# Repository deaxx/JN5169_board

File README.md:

# JN5169_board
mini-dev board on E75-2G4M10S

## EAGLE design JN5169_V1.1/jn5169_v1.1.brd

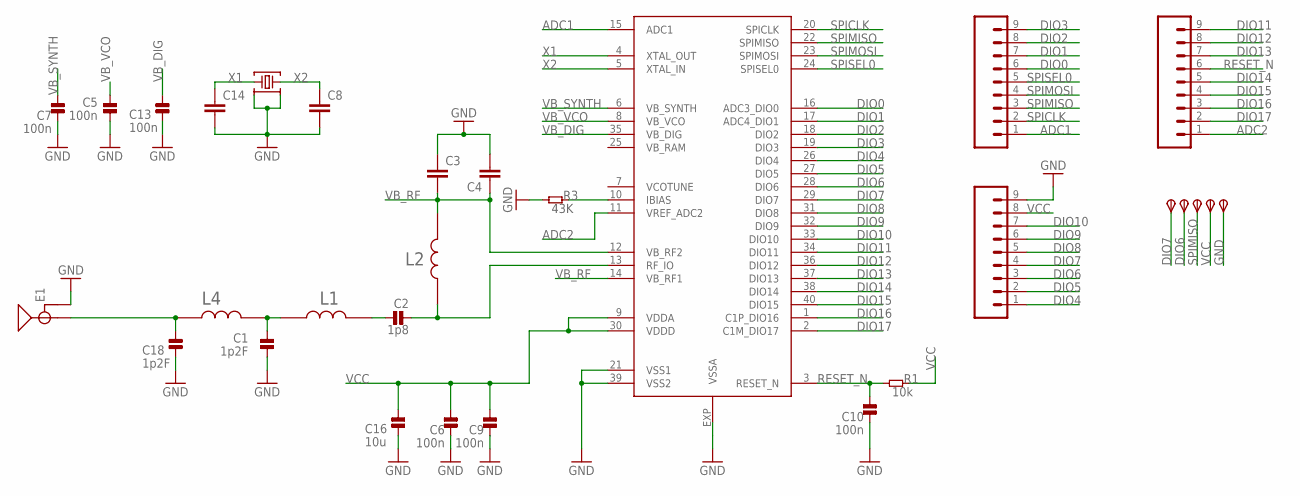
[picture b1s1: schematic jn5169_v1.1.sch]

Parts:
C1, C18: 1p2F; _PKG_C_0402
C2: 1p8; _PKG_C_0402
C3: 100n; CAPC1005X40N
C4: 47pf; CAPC1005X40N
C5, C6, C7, C9, C10, C13: 100n; _PKG_C_0402
C8, C14: 12p; CAPC1005X40N
C16: 10u; _PKG_C_0805
E1: ANTENNA-GROUNDEDTRACE-15.2MM; TRACE_ANTENNA_2.4GHZ_15.2MM
GND: TPSTP11R; TP11R
J1, J2, J3: CONN_051.27MM; 1X05_1.27MM
L1: 3n3H; INDC1005X40N
L2: 1n5H; INDC1005X40N
L4: 2n7H; INDC1005X40N
R1: 10k; _PKG_C_0402
R3: 43K; _PKG_C_0402
RX: TPSTP11R; TP11R
TDO: TPSTP11R; TP11R
TX: TPSTP11R; TP11R
U$1: JN5168/A02Z; QFN50P600X600X100-41N
VCC: TPSTP11R; TP11R
Y1: 32MHZ; XTAL-4P-2016

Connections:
ADC1: J1.1, U$1.15 (ADC1)
ADC2: J3.1, U$1.11 (VREF_ADC2)
DIO0: J1.6, U$1.16 (ADC3_DIO0)
DIO1: J1.7, U$1.17 (ADC4_DIO1)
DIO2: J1.8, U$1.18 (DIO2)
DIO3: J1.9, U$1.19 (DIO3)
DIO4: J2.1, U$1.26 (DIO4)
DIO5: J2.2, U$1.27 (DIO5)
DIO6: J2.3, TX.TP, U$1.28 (DIO6)
DIO7: J2.4, RX.TP, U$1.29 (DIO7)
DIO8: J2.5, U$1.31 (DIO8)
DIO9: J2.6, U$1.32 (DIO9)
DIO10: J2.7, U$1.33 (DIO10)
DIO11: J3.9, U$1.34 (DIO11)
DIO12: J3.8, U$1.36 (DIO12)
DIO13: J3.7, U$1.37 (DIO13)
DIO14: J3.5, U$1.38 (DIO14)
DIO15: J3.4, U$1.40 (DIO15)
DIO16: J3.3, U$1.1 (C1P_DIO16)
DIO17: J3.2, U$1.2 (C1M_DIO17)
GND: C1.1, C3.1, C4.2, C5.1, C6.1, C7.1, C8.2, C9.1, C10.1, C13.2, C14.2, C16.2, C18.2, E1.GND, GND.TP, J2.9, R3.2, U$1.21 (VSS1), U$1.39 (VSS2), U$1.EXP (VSSA), Y1.2, Y1.4
unnamed: C2.2, L1.2
unnamed: C2.1, L2.1, U$1.13 (RF_IO)
unnamed: C1.2, L1.1, L4.2
unnamed: C18.1, E1.ANT (SIGNAL), L4.1
unnamed: R3.1, U$1.10 (IBIAS)
RESET_N: C10.2, J3.6, R1.2, U$1.3 (RESET_N)
SPICLK: J1.2, U$1.20 (SPICLK)
SPIMISO: J1.3, TDO.TP, U$1.22 (SPIMISO)
SPIMOSI: J1.4, U$1.23 (SPIMOSI)
SPISEL0: J1.5, U$1.24 (SPISEL0)
VB_DIG: C13.1, U$1.35 (VB_DIG)
VB_RAM: U$1.25 (VB_RAM)
VB_RF: C3.2, C4.1, L2.2, U$1.12 (VB_RF2), U$1.14 (VB_RF1)
VB_SYNTH: C7.2, U$1.6 (VB_SYNTH)
VB_VCO: C5.2, U$1.8 (VB_VCO)
VCC: C6.2, C9.2, C16.1, J2.8, R1.1, U$1.9 (VDDA), U$1.30 (VDDD), VCC.TP
VCOTUNE: U$1.7 (VCOTUNE)
X1: C14.1, U$1.4 (XTAL_OUT), Y1.1
X2: C8.1, U$1.5 (XTAL_IN), Y1.3

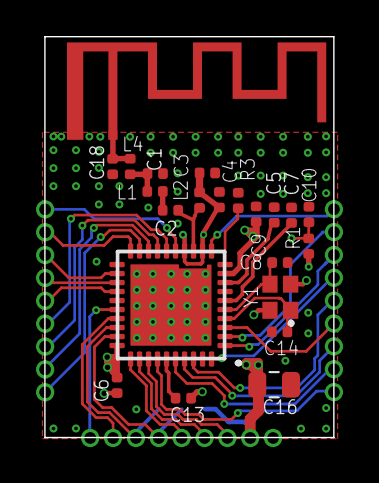
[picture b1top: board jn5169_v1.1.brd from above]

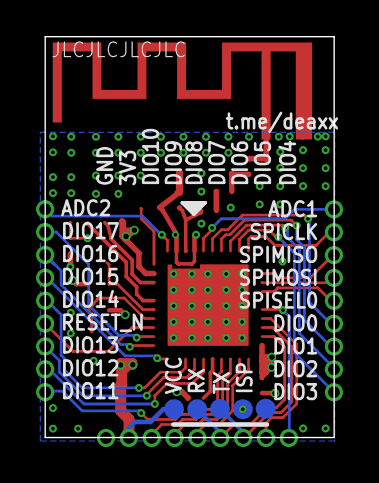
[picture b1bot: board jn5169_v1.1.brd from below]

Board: 4 copper layers, 16.1 x 22.3 mm, 30 parts (5 on the bottom side), 38 nets.

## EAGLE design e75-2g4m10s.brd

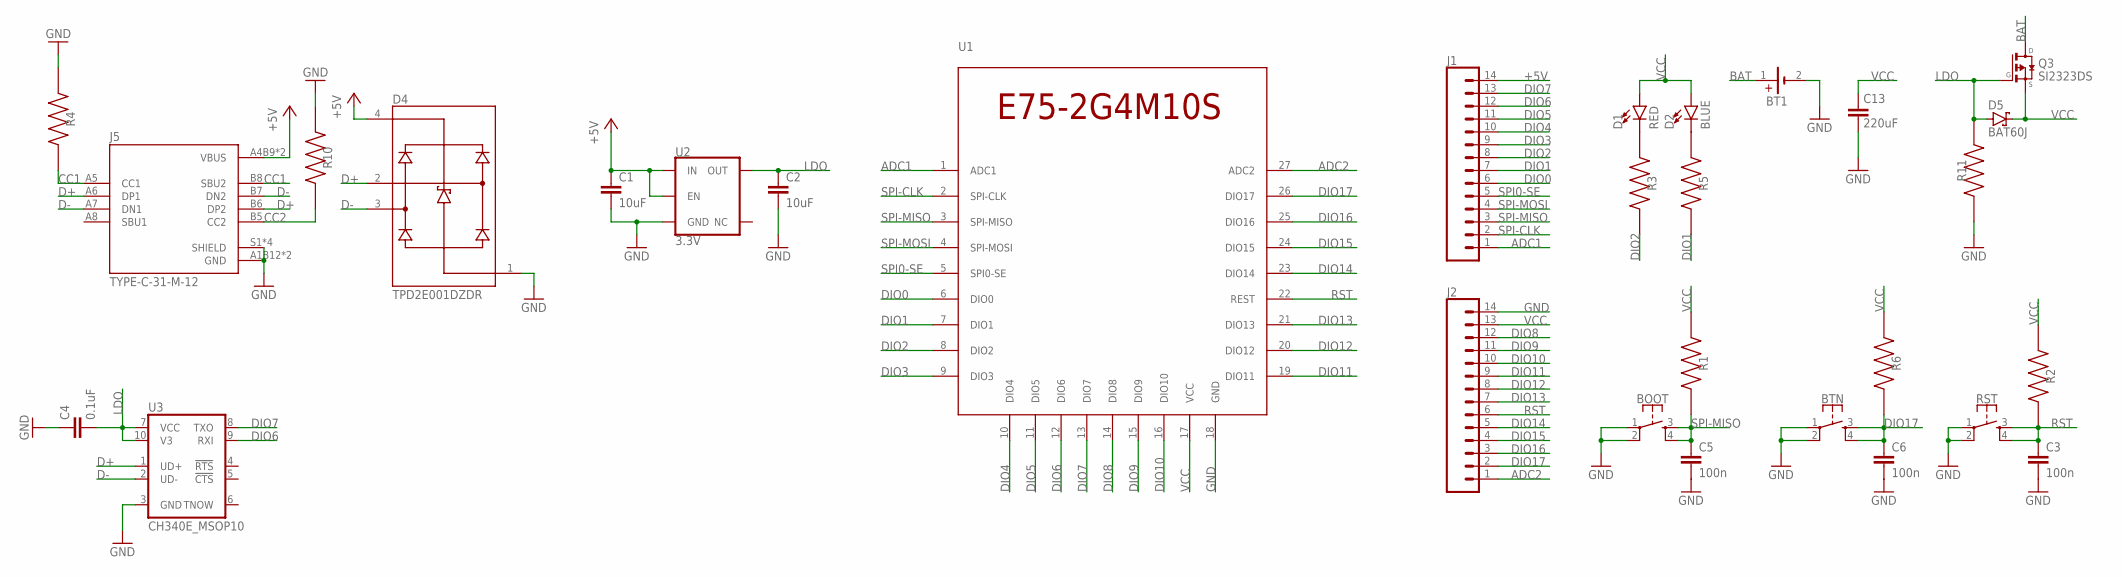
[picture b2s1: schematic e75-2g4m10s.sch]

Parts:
BOOT: MOMENTARY-SWITCH-SPST-2-SMD-4.6X2.8MM; TACTILE_SWITCH_SMD_4.6X2.8MM
BT1: 79527141
BTN: MOMENTARY-SWITCH-SPST-2-SMD-4.6X2.8MM; TACTILE_SWITCH_SMD_4.6X2.8MM
C1, C2: 10uF; 0603
C3, C5, C6: 100n; 0603
C4: 0.1uF; 0603
C13: 220uF; CAPM7343X310
D1: RED; LED-0603
D2: BLUE; LED-0603
D4: TPD2E001DZDR; SOT192P237X122-4N
D5: BAT60J; SOD323_ST
J1, J2: CONN_14NO_SILK; 1X14_NO_SILK
J5: TYPE-C-31-M-12; HRO_TYPE-C-31-M-12
Q3: SI2323DS; SOT23
R1, R2, R6, R11: 10k; RESC1005X40N
R3, R5: 2k; RESC1005X40N
R4, R10: 5.1k; RESC1005X40N
RST: MOMENTARY-SWITCH-SPST-2-SMD-4.6X2.8MM; TACTILE_SWITCH_SMD_4.6X2.8MM
U1: E73-2G4M04S1BE75-2G4M10S; E75-2G4M10S
U2: 3.3V; SOT23-5
U3: CH340E_MSOP10; MSOP10

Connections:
+5V: C1.1, D4.4 (VCC), J1.14, J5.A4B9 (VBUS), J5.B4A9 (VBUS), U2.1 (IN), U2.3 (EN)
ADC1: J1.1, U1.1 (ADC1)
ADC2: J2.1, U1.27 (ADC2)
BAT: BT1.1 (+), Q3.3 (D)
CC1: J5.A5 (CC1), J5.B8 (SBU2), R4.2
CC2: J5.B5 (CC2), R10.2
D+: D4.2 (IO1), J5.A6 (DP1), J5.B6 (DP2), U3.1 (UD+)
D-: D4.3 (IO2), J5.A7 (DN1), J5.B7 (DN2), U3.2 (UD-)
DIO0: J1.6, U1.6 (DIO0)
DIO1: J1.7, R5.2, U1.7 (DIO1)
DIO2: J1.8, R3.2, U1.8 (DIO2)
DIO3: J1.9, U1.9 (DIO3)
DIO4: J1.10, U1.10 (DIO4)
DIO5: J1.11, U1.11 (DIO5)
DIO6: J1.12, U1.12 (DIO6), U3.9 (RXI)
DIO7: J1.13, U1.13 (DIO7), U3.8 (TXO)
DIO8: J2.12, U1.14 (DIO8)
DIO9: J2.11, U1.15 (DIO9)
DIO10: J2.10, U1.16 (DIO10)
DIO11: J2.9, U1.19 (DIO11)
DIO12: J2.8, U1.20 (DIO12)
DIO13: J2.7, U1.21 (DIO13)
DIO14: J2.5, U1.23 (DIO14)
DIO15: J2.4, U1.24 (DIO15)
DIO16: J2.3, U1.25 (DIO16)
DIO17: BTN.3, BTN.4, C6.1, J2.2, R6.2, U1.26 (DIO17)
GND: BOOT.1, BOOT.2, BT1.2 (-), BTN.1, BTN.2, C1.2, C2.2, C3.2, C4.1, C5.2, C6.2, C13.2, D4.1 (GND), J2.14, J5.A1B12 (GND), J5.B1A12 (GND), J5.S1 (SHIELD), J5.S2 (SHIELD), J5.S3 (SHIELD), J5.S4 (SHIELD), R4.1, R10.1, R11.1, RST.1, RST.2, U1.18 (GND), U2.2 (GND), U3.3 (GND)
LDO: C2.1, C4.2, D5.A, Q3.1 (G), R11.2, U2.5 (OUT), U3.7 (VCC), U3.10 (V3)
unnamed: D1.C, R3.1
unnamed: D2.C, R5.1
RST: C3.1, J2.6, R2.2, RST.3, RST.4, U1.22 (REST)
SPI0-SE: J1.5, U1.5 (SPI0-SE)
SPI-CLK: J1.2, U1.2 (SPI-CLK)
SPI-MISO: BOOT.3, BOOT.4, C5.1, J1.3, R1.2, U1.3 (SPI-MISO)
SPI-MOSI: J1.4, U1.4 (SPI-MOSI)
VCC: C13.1, D1.A, D2.A, D5.C, J2.13, Q3.2 (S), R1.1, R2.1, R6.1, U1.17 (VCC)

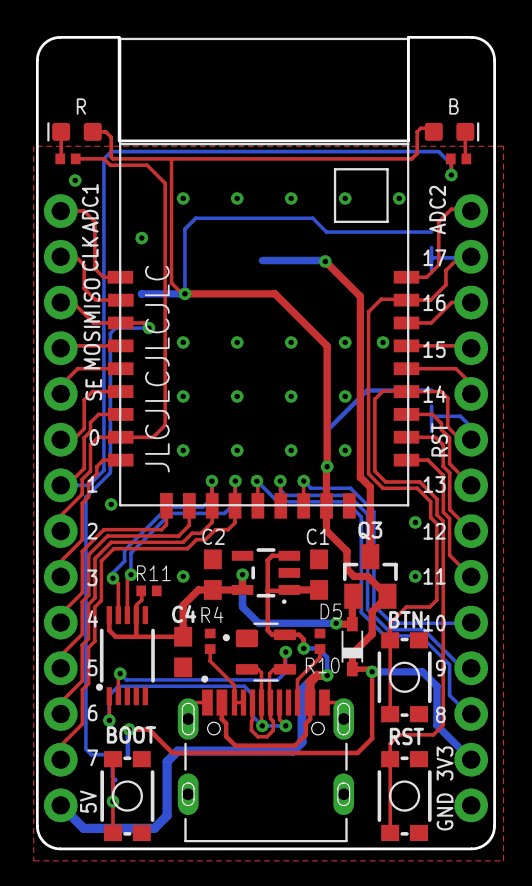
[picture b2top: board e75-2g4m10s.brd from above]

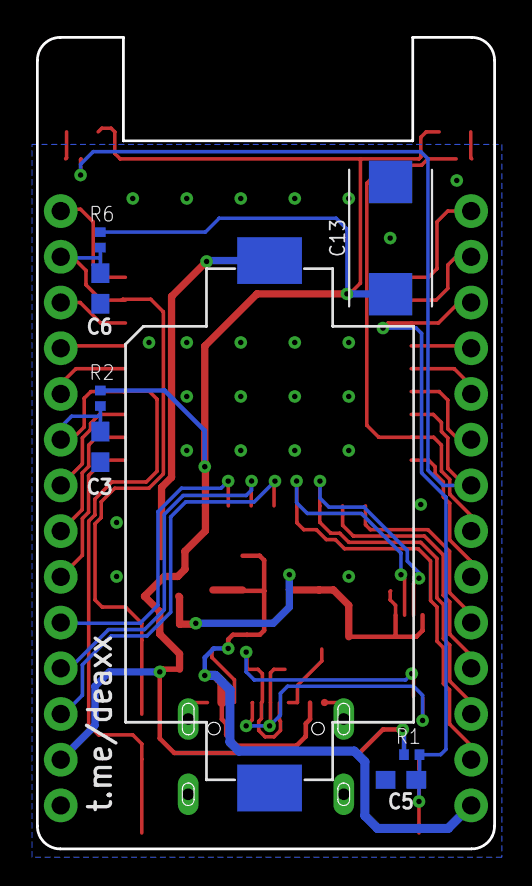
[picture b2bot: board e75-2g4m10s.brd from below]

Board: 2 copper layers, 25.4 x 45.1 mm, 30 parts (8 on the bottom side), 36 nets.

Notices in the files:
parts and their libraries:
SparkFun-Connectors: Licensing: Creative Commons ShareAlike 4.0 International - https://creativecommons.org/licenses/by-sa/4.0
